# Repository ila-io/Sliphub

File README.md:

# Sliphub
A USB hub that I can slip on and off of the top of my Surface Pro! 

It has 2 USB A ports and 2 USB C ports, and will fit on the top of my surface pro alongside my [slipboard](https://github.com/ila-io/slipboard/)! I modeled this after the design I made for that, and am hoping it's the second of a suite of slip-on accessories for my laptop :D

I made it because the surface pro only has 2 USB C ports, which is basically unusable for any considerable amount of wired devices (i.e. using it in place of a desktop with monitors, input devices, etc), and I didn't have a USB hub already! 

### heres what the product looks like!

(my friend didnt print out the top of the case in time, but i'll update this once I have it!) 

### [demo video!](https://youtu.be/sluuIp59PdY)

## BOM:
### PCBA BOM:
| item             | count | LCSC number | cost  | LCSC link                                                                                                                                                    |
|------------------|-------|-------------|-------|--------------------------------------------------------------------------------------------------------------------------------------------------------------|
| USB-C Receptacle |     3 | C3197885    | $2.99 | https://lcsc.com/product-detail/USB-Connectors_JAE-DX07S016JA1R1500_C3197885.html                                                                            |
| USB-A Receptacle |     2 | C2798029    | $1.63 | https://lcsc.com/product-detail/USB-Connectors_MOLEX-676430910_C2798029.html?s_z=n_USB%2520A%2520Molex%252067643                                             |
| SL2.1A           |     1 | C192893     | $0.26 | https://lcsc.com/product-detail/USB-HUB-Controllers_CoreChips-SL2-1A_C192893.html                                                                            |
| 100nF capacitor  |     5 | C48579599   | $0.25 | https://lcsc.com/product-detail/Multilayer-Ceramic-Capacitors-MLCC-SMD-SMT_AIDE-CAPACITOR-0805X7R104K101NT_C48579599.html?s_z=n_0805%2520100nf%2520capacitor |
| 10uF capacitor   |     2 | C48579582   | $0.71 | https://lcsc.com/product-detail/Multilayer-Ceramic-Capacitors-MLCC-SMD-SMT_AIDE-CAPACITOR-0805X5R106K500NT_C48579582.html?s_z=n_10uf%2520capacitor%25200805  |
| 5.1k Ω resistor  |     2 | C27834      | $0.19 | https://lcsc.com/product-detail/Chip-Resistor-Surface-Mount_UNI-ROYAL-0805W8F5101T5E_C27834.html?s_z=n_0805%25205.1k%2520ohm%2520resistor                    |
| 56k Ω resistor   |     4 | C17756      | $0.19 | https://lcsc.com/product-detail/Chip-Resistor-Surface-Mount_UNI-ROYAL-0805W8F5602T5E_C17756.html?s_z=n_0805%252056k%2520ohm%2520resistor                     |
| Diode            |     1 | C154551     | $0.57 | https://lcsc.com/product-detail/Schottky-Diodes_onsemi-SS34_C154551.html?s_z=n_SS34                                                                          |
PCBA Cost | | |$37.83

### GENERAL BOM: 
| item                        | count             | cost   | link                                                                                                                                                                                                                                                                                                                                                                                                                                                                                                                                                                                                 |
|-----------------------------|-------------------|--------|------------------------------------------------------------------------------------------------------------------------------------------------------------------------------------------------------------------------------------------------------------------------------------------------------------------------------------------------------------------------------------------------------------------------------------------------------------------------------------------------------------------------------------------------------------------------------------------------------|
| PCBA                        | 2 (minimum order) | $37.83 | https://jlcpcb.com                                                                                                                                                                                                                                                                                                                                                                                                                                                                                                                                                                                   |
| M2 Heatset Inserts x50      | 1                 |  $0.99 | https://www.aliexpress.us/item/3256803396040989.html?spm=a2g0o.productlist.main.1.5fe1tUQQtUQQ7l&algo_pvid=d7b60f0b-e780-4759-b797-b2f6e887de47&algo_exp_id=d7b60f0b-e780-4759-b797-b2f6e887de47-0&pdp_ext_f=%7B%22order%22%3A%2218161%22%2C%22eval%22%3A%221%22%7D&pdp_npi=4%40dis!USD!1.74!0.99!!!1.74!0.99!%402103010e17534347345916170e1408!12000026370649723!sea!US!6404024211!ABX&curPageLogUid=zXRdRmildqGP&utparam-url=scene%3Asearch%7Cquery_from%3A                                                                                                                                        |
| M2 Screws x50               | 1                 |  $0.99 | https://www.aliexpress.us/item/3256802178253461.html?spm=a2g0o.productlist.main.4.94783ca75RQUAA&aem_p4p_detail=202507261801262939809493575570002980427&algo_pvid=d776e6f8-0569-4ccb-b633-1f90a9f39bb8&algo_exp_id=d776e6f8-0569-4ccb-b633-1f90a9f39bb8-3&pdp_ext_f=%7B%22order%22%3A%22723%22%2C%22eval%22%3A%221%22%7D&pdp_npi=4%40dis%21USD%211.55%210.99%21%21%211.55%210.99%21%402103241117535780862826083e5eee%2112000020355723604%21sea%21US%216404024211%21ABX&curPageLogUid=juaZaL7nG3yR&utparam-url=scene%3Asearch%7Cquery_from%3A&search_p4p_id=202507261801262939809493575570002980427_1 |
| 1.5mm silicone rubber sheet | 1                 | $4.76  | https://www.aliexpress.us/item/3256801236853786.html?spm=a2g0o.productlist.main.1.2d39VEjxVEjx6E&algo_pvid=fcf873a6-e901-4e9f-94e9-011e1f1275f9&algo_exp_id=fcf873a6-e901-4e9f-94e9-011e1f1275f9-0&pdp_ext_f=%7B%22order%22%3A%2212%22%2C%22eval%22%3A%221%22%7D&pdp_npi=4%40dis%21USD%219.53%214.76%21%21%219.53%214.76%21%402101eab017535801062311728e74e6%2112000016056354201%21sea%21US%216404024211%21ABX&curPageLogUid=UNVC3Bw02WfL&utparam-url=scene%3Asearch%7Cquery_from%3A                                                                                                                 |
| total:                      | 5                 | $44.75 |                                                                                                                                                                                                                                                                                                                                                                                                                                                                                                                                                                                                      |

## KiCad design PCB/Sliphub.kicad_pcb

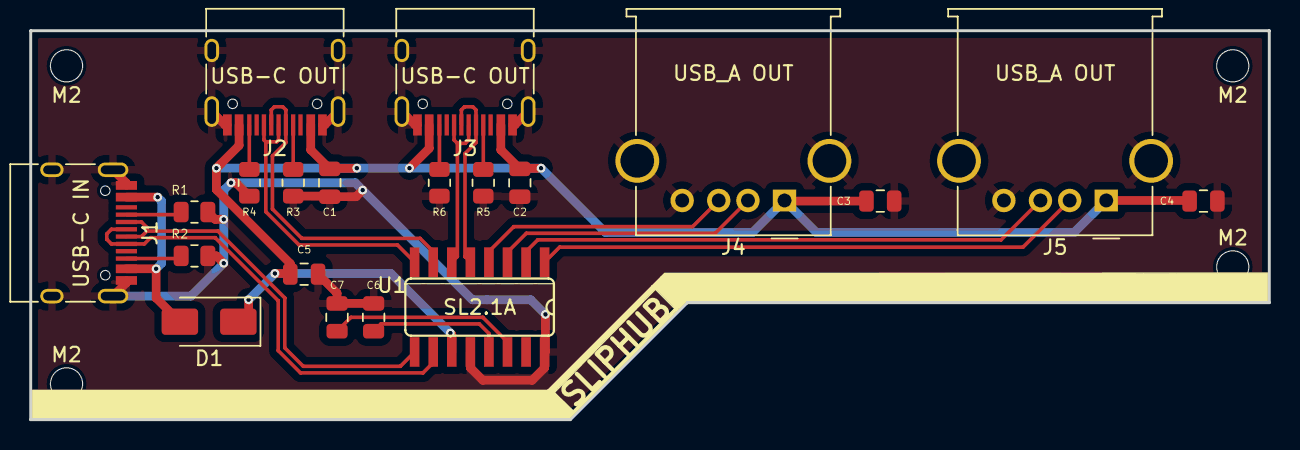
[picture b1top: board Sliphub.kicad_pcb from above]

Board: 2 copper layers, 84.7 x 26.6 mm, 24 parts (0 on the bottom side), 21 nets.

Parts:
C1, C2, C3, C4, C5: 100nF; C_0805_2012Metric
C6, C7: 10uF; C_0805_2012Metric
D1: D_SMA
J1: USB-C IN; USB_C_Receptacle_HRO_TYPE-C-31-M-12
J2, J3: USB-C OUT; USB_C_Receptacle_HRO_TYPE-C-31-M-12
J4, J5: USB_A OUT; USB_A_Molex_67643_Horizontal
M2, M2#2, M2#3, M2#4: M2; MountingHole_2.2mm_M2
R1, R2: 5.1k Ω; R_0805_2012Metric
R3, R4, R5, R6: 56kΩ; R_0805_2012Metric
U1: SL2.1A; SO16

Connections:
D1+: J2.A6 (D+), J2.B6 (D+), U1.8 (DP1)
D1-: J2.A7 (D-), J2.B7 (D-), U1.7 (DM1)
D2+: J3.A6 (D+), J3.B6 (D+), U1.6 (DP2)
D2-: J3.A7 (D-), J3.B7 (D-), U1.5 (DM2)
D3+: J4.3 (D+), U1.4 (DP3)
D3-: J4.2 (D-), U1.3 (DM3)
D4+: J5.3 (D+), U1.2 (DP4)
D4-: J5.2 (D-), U1.1 (DM4)
D+: J1.A6 (D+), J1.B6 (D+), U1.10 (DP)
D-: J1.A7 (D-), J1.B7 (D-), U1.9 (DM)
GND: C1.2, C2.2, C3.2, C4.2, C5.2, C6.2, C7.2, J1.A1 (GND), J1.A12 (GND), J1.B1 (GND), J1.B12 (GND), J1.S1 (SHIELD), J2.A1 (GND), J2.A12 (GND), J2.B1 (GND), J2.B12 (GND), J2.S1 (SHIELD), J3.A1 (GND), J3.A12 (GND), J3.B1 (GND), J3.B12 (GND), J3.S1 (SHIELD), J4.4 (GND), J4.5 (Shield), J5.4 (GND), J5.5 (Shield), R1.2, R2.2, R3.2, R4.2, R5.2, R6.2, U1.12 (GND), U1.16 (XIN)
unnamed: D1.2 (A), J1.A4 (VBUS), J1.A9 (VBUS), J1.B4 (VBUS), J1.B9 (VBUS)
unnamed: J1.A5 (CC1), R1.1
unnamed: J1.B5 (CC2), R2.1
unnamed: J2.A5 (CC1), R3.1
unnamed: J2.B5 (CC2), R4.1
unnamed: J3.A5 (CC1), R5.1
unnamed: J3.B5 (CC2), R6.1
unnamed: C7.1, U1.14 (VDD18)
unnamed: C6.1, U1.13 (VDD33)
VBUS: C1.1, C2.1, C3.1, C4.1, C5.1, D1.1 (K), J2.A4 (VBUS), J2.A9 (VBUS), J2.B4 (VBUS), J2.B9 (VBUS), J3.A4 (VBUS), J3.A9 (VBUS), J3.B4 (VBUS), J3.B9 (VBUS), J4.1 (VBUS), J5.1 (VBUS), U1.11 (VDD5)

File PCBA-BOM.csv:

item,count,LCSC number,cost,LCSC link
USB-C Receptacle,3,C3197885,$2.99,https://lcsc.com/product-detail/USB-Connectors_JAE-DX07S016J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
USB-A Receptacle,2,C2798029,$1.63,https://lcsc.com/product-detail/USB-Connectors_MOLEX-6764309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
SL2.1A,1,C192893,$0.26,https://lcsc.com/product-detail/USB-HUB-Controllers_CoreChip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
100nF capacitor,5,C48579599,$0.25,https://lcsc.com/product-detail/Multilayer-Ceramic-Capacitor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
10uF capacitor,2,C48579582,$0.71,https://lcsc.com/product-detail/Multilayer-Ceramic-Capacitor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
5.1k Ω resistor,2,C27834,$0.19,https://lcsc.com/product-detail/Chip-Resistor-Surface-Mount_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
56k Ω resistor,4,C17756,$0.19,https://lcsc.com/product-detail/Chip-Resistor-Surface-Mount_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
Diode,1,C8678,$0.57,https://lcsc.com/product-detail/Schottky-Diodes_MDD-Microdio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

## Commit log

2025-07-25 Add photos
2025-07-27 Add production, case, and pcb files
2025-07-27 Rename image.png to schematic.png
2025-07-27 add BOMs
2025-07-27 add BOM for JLCPCB for PCBA
